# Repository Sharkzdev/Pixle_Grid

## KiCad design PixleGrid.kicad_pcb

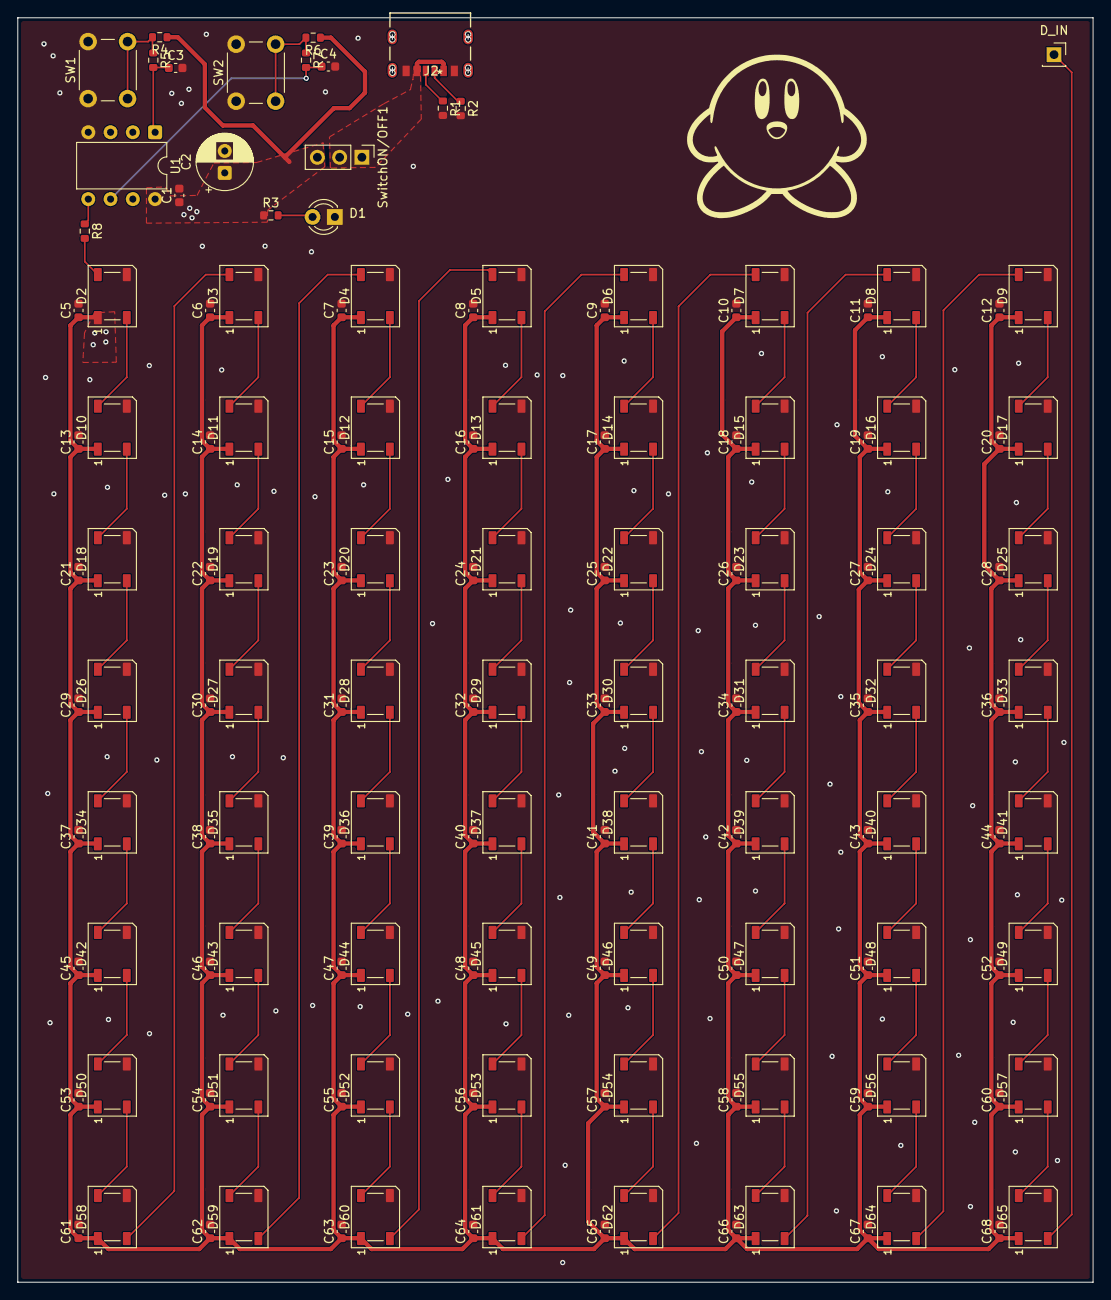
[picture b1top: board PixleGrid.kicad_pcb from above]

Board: 2 copper layers, 122.6 x 144.2 mm, 147 parts (0 on the bottom side), 12 nets.

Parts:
C1: 10uF; C_0603_1608Metric
C2: 470uF; CP_Radial_D6.3mm_P2.50mm
C3, C4: 1000nF; C_0603_1608Metric
C5, C6, C7, C8, C9, C10, C11, C12, C13, C14, C15, C16, C17, C18, C19, C20, C21, C22, C23, C24, C25, C26, C27, C28, C29, C30, C31, C32, C33, C34, C35, C36, C37, C38, C39, C40, C41, C42, C43, C44, C45, C46, C47, C48, C49, C50, C51, C52, C53, C54, C55, C56, C57, C58, C59, C60, C61, C62, C63, C64, C65, C66, C67, C68: 100nF; C_0603_1608Metric
D1: LED; LED_D3.0mm
D2, D3, D4, D5, D6, D7, D8, D9, D10, D11, D12, D13, D14, D15, D16, D17, D18, D19, D20, D21, D22, D23, D24, D25, D26, D27, D28, D29, D30, D31, D32, D33, D34, D35, D36, D37, D38, D39, D40, D41, D42, D43, D44, D45, D46, D47, D48, D49, D50, D51, D52, D53, D54, D55, D56, D57, D58, D59, D60, D61, D62, D63, D64, D65: WS2812B; LED_WS2812B_PLCC4_5.0x5.0mm_P3.2mm
D_IN: PinSocket_1x01_P2.54mm_Vertical
J2: 2171750001; 2171750001_MOL
R1, R2: 5K1; R_0603_1608Metric
R3: 510R; R_0603_1608Metric
R4, R6: 10k; R_0603_1608Metric
R5, R7: 0R; R_0603_1608Metric
R8: 310R; R_0603_1608Metric
SW1, SW2: SW_Push; SW_PUSH_6mm
SwitchON/OFF1: Conn_01x03; PinHeader_1x03_P2.54mm_Vertical
U1: ATtiny85-20P; DIP-8_W7.62mm

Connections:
+5V: J2.A9 (VBUS_2), J2.B9 (VBUS), SwitchON/OFF1.1, SwitchON/OFF1.2
D_IN: D2.2 (DOUT), D2.4 (DIN), D3.2 (DOUT), D3.4 (DIN), D4.2 (DOUT), D4.4 (DIN), D5.2 (DOUT), D5.4 (DIN), D6.2 (DOUT), D6.4 (DIN), D7.2 (DOUT), D7.4 (DIN), D8.2 (DOUT), D8.4 (DIN), D9.2 (DOUT), D9.4 (DIN), D10.2 (DOUT), D10.4 (DIN), D11.2 (DOUT), D11.4 (DIN), D12.2 (DOUT), D12.4 (DIN), D13.2 (DOUT), D13.4 (DIN), D14.2 (DOUT), D14.4 (DIN), D15.2 (DOUT), D15.4 (DIN), D16.2 (DOUT), D16.4 (DIN), D17.2 (DOUT), D17.4 (DIN), D18.2 (DOUT), D18.4 (DIN), D19.2 (DOUT), D19.4 (DIN), D20.2 (DOUT), D20.4 (DIN), D21.2 (DOUT), D21.4 (DIN), D22.2 (DOUT), D22.4 (DIN), D23.2 (DOUT), D23.4 (DIN), D24.2 (DOUT), D24.4 (DIN), D25.2 (DOUT), D25.4 (DIN), D26.2 (DOUT), D26.4 (DIN), D27.2 (DOUT), D27.4 (DIN), D28.2 (DOUT), D28.4 (DIN), D29.2 (DOUT), D29.4 (DIN), D30.2 (DOUT), D30.4 (DIN), D31.2 (DOUT), D31.4 (DIN), D32.2 (DOUT), D32.4 (DIN), D33.2 (DOUT), D33.4 (DIN), D34.2 (DOUT), D34.4 (DIN), D35.2 (DOUT), D35.4 (DIN), D36.2 (DOUT), D36.4 (DIN), D37.2 (DOUT), D37.4 (DIN), D38.2 (DOUT), D38.4 (DIN), D39.2 (DOUT), D39.4 (DIN), D40.2 (DOUT), D40.4 (DIN), D41.2 (DOUT), D41.4 (DIN), D42.2 (DOUT), D42.4 (DIN), D43.2 (DOUT), D43.4 (DIN), D44.2 (DOUT), D44.4 (DIN), D45.2 (DOUT), D45.4 (DIN), D46.2 (DOUT), D46.4 (DIN), D47.2 (DOUT), D47.4 (DIN), D48.2 (DOUT), D48.4 (DIN), D49.2 (DOUT), D49.4 (DIN), D50.2 (DOUT), D50.4 (DIN), D51.2 (DOUT), D51.4 (DIN), D52.2 (DOUT), D52.4 (DIN), D53.2 (DOUT), D53.4 (DIN), D54.2 (DOUT), D54.4 (DIN), D55.2 (DOUT), D55.4 (DIN), D56.2 (DOUT), D56.4 (DIN), D57.2 (DOUT), D57.4 (DIN), D58.2 (DOUT), D58.4 (DIN), D59.2 (DOUT), D59.4 (DIN), D60.2 (DOUT), D60.4 (DIN), D61.2 (DOUT), D61.4 (DIN), D62.2 (DOUT), D62.4 (DIN), D63.2 (DOUT), D63.4 (DIN), D64.2 (DOUT), D64.4 (DIN), D65.2 (DOUT), D65.4 (DIN), D_IN.1, R8.2
GND: C1.2, C2.2, C3.2, C4.2, C5.2, C6.2, C7.2, C8.2, C9.2, C10.2, C11.2, C12.2, C13.2, C14.2, C15.2, C16.2, C17.2, C18.2, C19.2, C20.2, C21.2, C22.2, C23.2, C24.2, C25.2, C26.2, C27.2, C28.2, C29.2, C30.2, C31.2, C32.2, C33.2, C34.2, C35.2, C36.2, C37.2, C38.2, C39.2, C40.2, C41.2, C42.2, C43.2, C44.2, C45.2, C46.2, C47.2, C48.2, C49.2, C50.2, C51.2, C52.2, C53.2, C54.2, C55.2, C56.2, C57.2, C58.2, C59.2, C60.2, C61.2, C62.2, C63.2, C64.2, C65.2, C66.2, C67.2, C68.2, D1.1 (K), D2.3 (VSS), D3.3 (VSS), D4.3 (VSS), D5.3 (VSS), D6.3 (VSS), D7.3 (VSS), D8.3 (VSS), D9.3 (VSS), D10.3 (VSS), D11.3 (VSS), D12.3 (VSS), D13.3 (VSS), D14.3 (VSS), D15.3 (VSS), D16.3 (VSS), D17.3 (VSS), D18.3 (VSS), D19.3 (VSS), D20.3 (VSS), D21.3 (VSS), D22.3 (VSS), D23.3 (VSS), D24.3 (VSS), D25.3 (VSS), D26.3 (VSS), D27.3 (VSS), D28.3 (VSS), D29.3 (VSS), D30.3 (VSS), D31.3 (VSS), D32.3 (VSS), D33.3 (VSS), D34.3 (VSS), D35.3 (VSS), D36.3 (VSS), D37.3 (VSS), D38.3 (VSS), D39.3 (VSS), D40.3 (VSS), D41.3 (VSS), D42.3 (VSS), D43.3 (VSS), D44.3 (VSS), D45.3 (VSS), D46.3 (VSS), D47.3 (VSS), D48.3 (VSS), D49.3 (VSS), D50.3 (VSS), D51.3 (VSS), D52.3 (VSS), D53.3 (VSS), D54.3 (VSS), D55.3 (VSS), D56.3 (VSS), D57.3 (VSS), D58.3 (VSS), D59.3 (VSS), D60.3 (VSS), D61.3 (VSS), D62.3 (VSS), D63.3 (VSS), D64.3 (VSS), D65.3 (VSS), J2.A12 (GND_2), J2.B12 (GND), R1.2, R2.2, SW1.1, SW2.1, U1.4 (GND)
MODE(PB1): C4.1, R7.2, U1.6 (PB1)
unnamed: D1.2 (A), R3.2
unnamed: J2.A5 (CC1), R2.1
unnamed: J2.B5 (CC2), R1.1
unnamed: R4.2, R5.1, SW1.2
unnamed: R6.2, R7.1, SW2.2
unnamed: R8.1, U1.5 (AREF/PB0)
RST(PB5): C3.1, R5.2, U1.1 (~RESET/PB5)
VCC: C1.1, C2.1, C5.1, C6.1, C7.1, C8.1, C9.1, C10.1, C11.1, C12.1, C13.1, C14.1, C15.1, C16.1, C17.1, C18.1, C19.1, C20.1, C21.1, C22.1, C23.1, C24.1, C25.1, C26.1, C27.1, C28.1, C29.1, C30.1, C31.1, C32.1, C33.1, C34.1, C35.1, C36.1, C37.1, C38.1, C39.1, C40.1, C41.1, C42.1, C43.1, C44.1, C45.1, C46.1, C47.1, C48.1, C49.1, C50.1, C51.1, C52.1, C53.1, C54.1, C55.1, C56.1, C57.1, C58.1, C59.1, C60.1, C61.1, C62.1, C63.1, C64.1, C65.1, C66.1, C67.1, C68.1, D2.1 (VDD), D3.1 (VDD), D4.1 (VDD), D5.1 (VDD), D6.1 (VDD), D7.1 (VDD), D8.1 (VDD), D9.1 (VDD), D10.1 (VDD), D11.1 (VDD), D12.1 (VDD), D13.1 (VDD), D14.1 (VDD), D15.1 (VDD), D16.1 (VDD), D17.1 (VDD), D18.1 (VDD), D19.1 (VDD), D20.1 (VDD), D21.1 (VDD), D22.1 (VDD), D23.1 (VDD), D24.1 (VDD), D25.1 (VDD), D26.1 (VDD), D27.1 (VDD), D28.1 (VDD), D29.1 (VDD), D30.1 (VDD), D31.1 (VDD), D32.1 (VDD), D33.1 (VDD), D34.1 (VDD), D35.1 (VDD), D36.1 (VDD), D37.1 (VDD), D38.1 (VDD), D39.1 (VDD), D40.1 (VDD), D41.1 (VDD), D42.1 (VDD), D43.1 (VDD), D44.1 (VDD), D45.1 (VDD), D46.1 (VDD), D47.1 (VDD), D48.1 (VDD), D49.1 (VDD), D50.1 (VDD), D51.1 (VDD), D52.1 (VDD), D53.1 (VDD), D54.1 (VDD), D55.1 (VDD), D56.1 (VDD), D57.1 (VDD), D58.1 (VDD), D59.1 (VDD), D60.1 (VDD), D61.1 (VDD), D62.1 (VDD), D63.1 (VDD), D64.1 (VDD), D65.1 (VDD), R3.1, R4.1, R6.1, SwitchON/OFF1.3, U1.8 (VCC)
